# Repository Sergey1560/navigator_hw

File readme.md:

# Navigator HW

Bluetooth-адаптер одометра для программы "[TSD Navigator](http://tsdnavigator.com/index.html)". Аналог [оригинального адаптера](http://tsdnavigator.com/v1/greybox.htm) 

[Схема](./navigator.pdf)

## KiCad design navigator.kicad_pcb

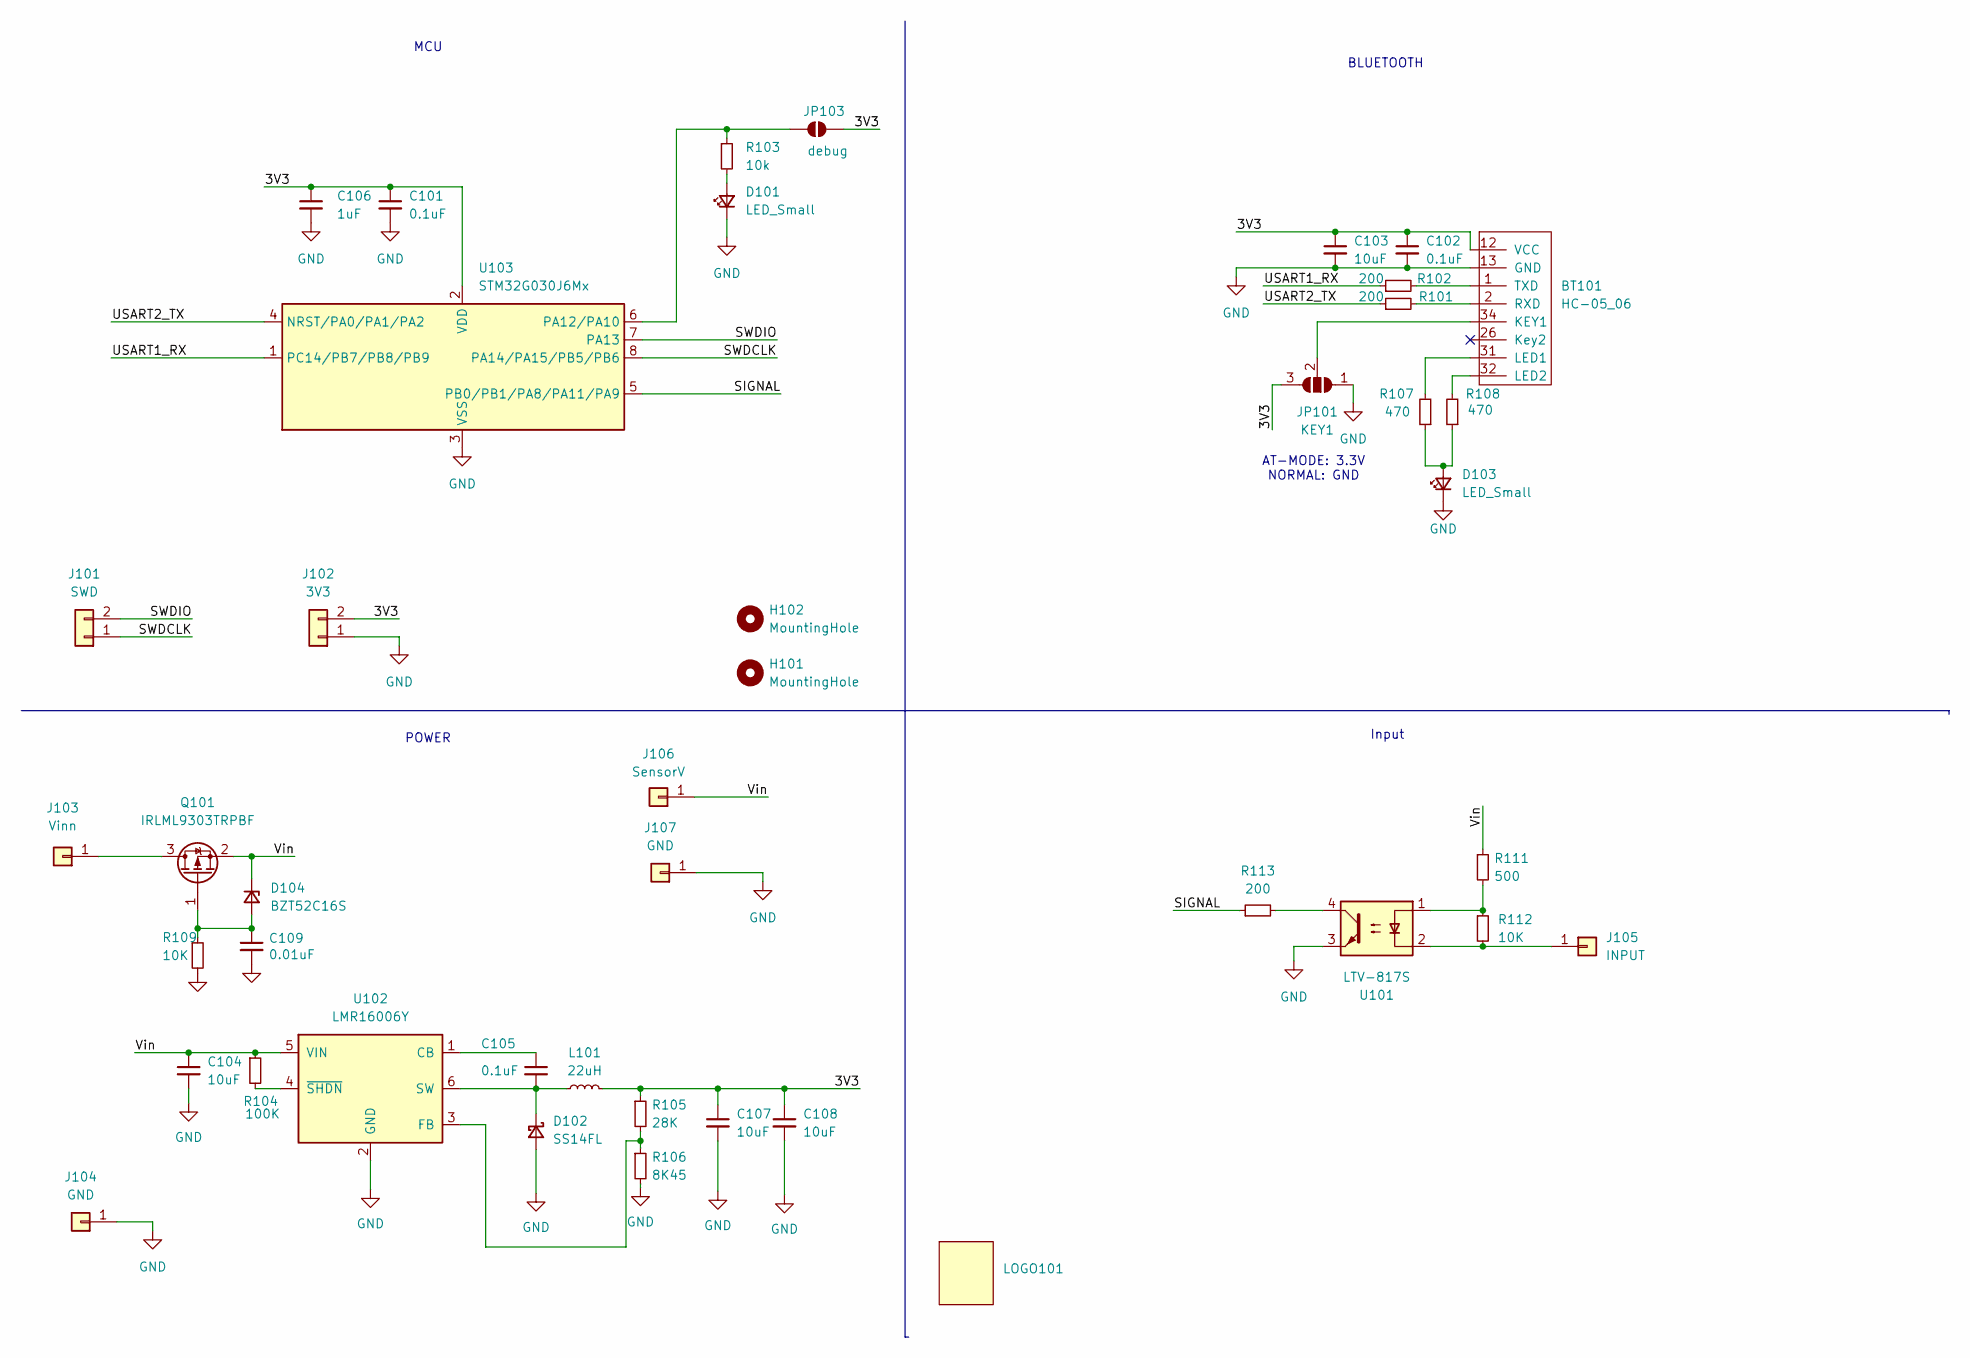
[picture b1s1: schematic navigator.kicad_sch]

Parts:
BT101: HC-05_06; HC-05
C101, C102: 0.1uF; C_0805_2012Metric
C103: 10uF; C_0805_2012Metric
C104, C107, C108: 10uF; C_0805_2012Metric; LCSC C440198
C105: 0.1uF; C_0805_2012Metric; LCSC C14663
C106: 1uF; C_0805_2012Metric
C109: 0.01uF; C_0603_1608Metric
D101, D103: LED_Small; LED_1206_3216Metric
D102: SS14FL; D_SMF; LCSC C111580
D104: BZT52C16S; D_SOD-323
H101, H102: MountingHole; MountingHole_3.2mm_M3
J101: SWD; PinHeader_1x02_P2.54mm_Vertical
J102: 3V3; PinHeader_1x02_P2.54mm_Vertical
J103: Vinn; PinHeader_1x01_P2.54mm_Vertical
J104, J107: GND; PinHeader_1x01_P2.54mm_Vertical
J105: INPUT; PinHeader_1x01_P2.54mm_Vertical
J106: SensorV; PinHeader_1x01_P2.54mm_Vertical
JP101: KEY1; SolderJumper-3_P1.3mm_Open_RoundedPad1.0x1.5mm
JP103: debug; SolderJumper-2_P1.3mm_Open_Pad1.0x1.5mm
L101: 22uH; FNR5040S220MT; LCSC C167971
LOGO101: logo_15x9
Q101: IRLML9303TRPBF; SOT-23
R101, R102, R113: 200; R_0805_2012Metric
R103: 10k; R_0805_2012Metric
R104: 100K; R_0603_1608Metric; LCSC C163504
R105: 28K; R_0603_1608Metric; LCSC C728593
R106: 8K45; R_0603_1608Metric; LCSC C98220
R107, R108: 470; R_0805_2012Metric
R109: 10K; R_0603_1608Metric
R111: 500; R_0805_2012Metric
R112: 10K; R_0805_2012Metric
U101: LTV-817S; SMDIP-4_W9.53mm
U102: LMR16006Y; SOT-23-6; LCSC C290195
U103: STM32G030J6Mx; SOIC-8_3.9x4.9mm_P1.27mm

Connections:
/3V3: BT101.12 (VCC), C101.1, C102.1, C103.1, C106.1, C107.1, C108.1, J102.2, JP101.3 (B), JP103.2 (B), L101.2, R105.1, U103.2 (VDD)
/SIGNAL: R113.1, U103.5 (PB0/PB1/PA8/PA11/PA9)
/SWDCLK: J101.1, U103.8 (PA14/PA15/PB5/PB6)
/SWDIO: J101.2, U103.7 (PA13)
/USART1_RX: R102.1, U103.1 (PC14/PB7/PB8/PB9)
/USART2_TX: R101.1, U103.4 (NRST/PA0/PA1/PA2)
/Vin: C104.1, D104.1 (K), J106.1, Q101.2 (S), R104.1, R111.1, U102.5 (VIN)
GND: BT101.13 (GND), C101.2, C102.2, C103.2, C104.2, C106.2, C107.2, C108.2, C109.2, D101.1 (K), D102.2 (A), D103.1 (K), J102.1, J104.1, J107.1, JP101.1 (A), R106.2, R109.2, U101.3, U102.2 (GND), U103.3 (VSS)
unnamed: BT101.34 (KEY1), JP101.2 (C)
unnamed: BT101.31 (LED1), R107.2
unnamed: BT101.32 (LED2), R108.2
unnamed: BT101.2 (RXD), R101.2
unnamed: BT101.1 (TXD), R102.2
unnamed: D101.2 (A), R103.2
unnamed: C105.2, D102.1 (K), L101.1, U102.6 (SW)
unnamed: D103.2 (A), R107.1, R108.1
unnamed: C109.1, D104.2 (A), Q101.1 (G), R109.1
unnamed: J103.1, Q101.3 (D)
unnamed: J105.1, R112.2, U101.2
unnamed: JP103.1 (A), R103.1, U103.6 (PA12/PA10)
unnamed: R111.2, R112.1, U101.1
unnamed: R113.2, U101.4
unnamed: C105.1, U102.1 (CB)
unnamed: R105.2, R106.1, U102.3 (FB)
unnamed: R104.2, U102.4 (~SHDN)

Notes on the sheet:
MCU
BLUETOOTH
Input
POWER
AT-MODE: 3.3V NORMAL: GND

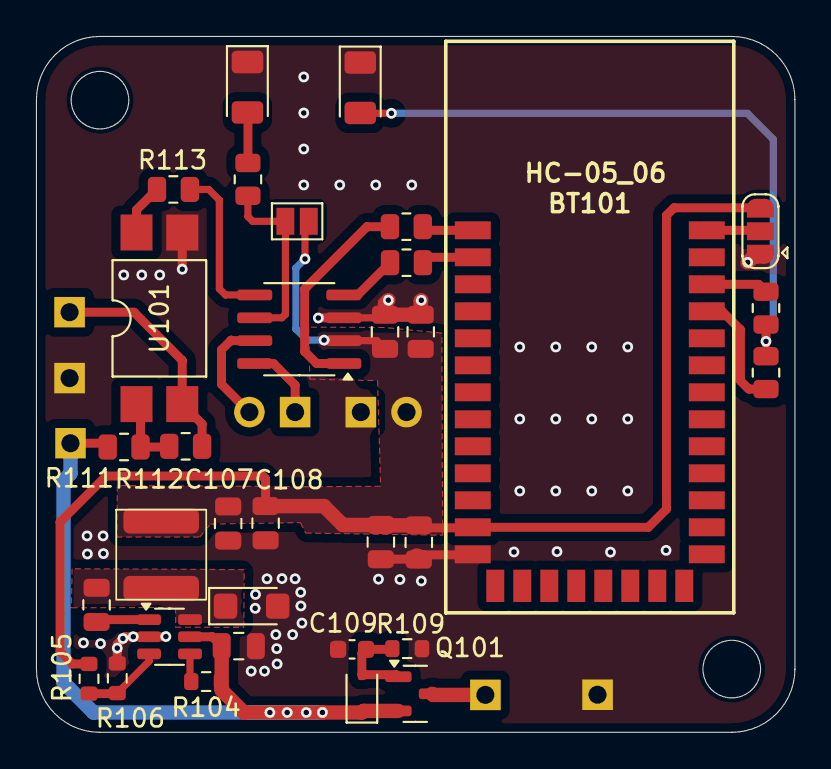
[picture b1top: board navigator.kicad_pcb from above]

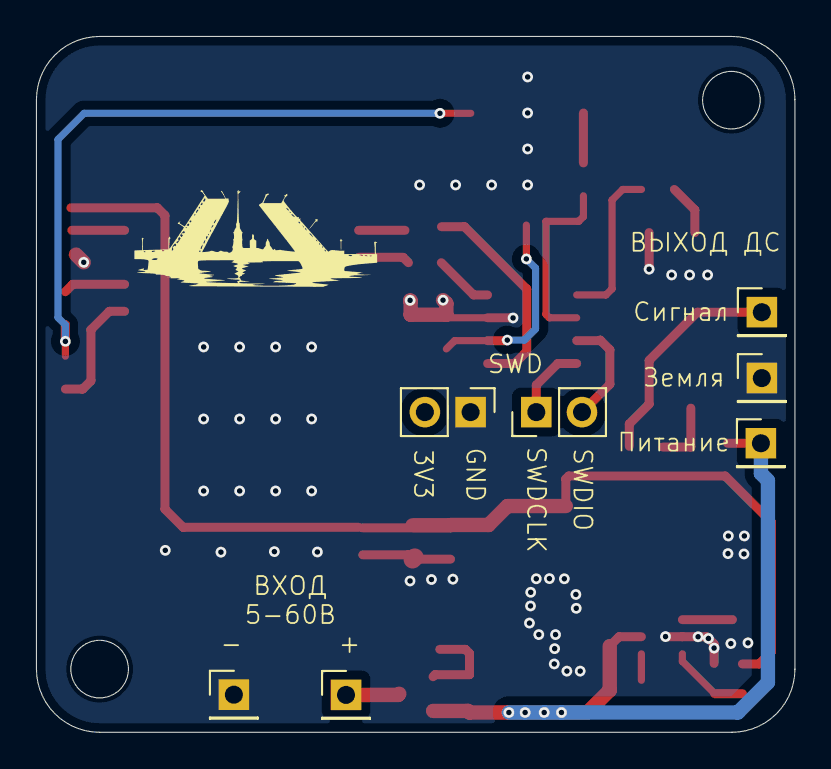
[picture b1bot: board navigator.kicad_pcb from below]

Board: 2 copper layers, 42.1 x 38.7 mm, 43 parts (8 on the bottom side), 25 nets.

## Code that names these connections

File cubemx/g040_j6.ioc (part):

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Mcu.Name=STM32G030J6Mx
Mcu.Package=SO8N
Mcu.UserName=STM32G030J6Mx
PA12\ [PA10].Signal=GPIO_Output
PA13.Mode=Serial_Wire
PA13.Signal=SYS_SWDIO
PA14-BOOT0.Mode=Serial_Wire
PA14-BOOT0.Signal=SYS_SWCLK
PA14-BOOT0__PA15__PB5__PB6.StandardMode=true
PA2.Signal=USART2_TX
PB0__PB1__PA8__PA11\ [PA9].StandardMode=true
PB1.Signal=S_TIM14_CH1
PB7.Signal=USART1_RX
PC14-OSC32_IN\ (PC14)__PB7__PB8__PB9.StandardMode=true
RCC.HSE_VALUE=8000000
RCC.SYSCLKFreq_VALUE=64000000
RCC.SYSCLKSource=RCC_SYSCLKSOURCE_PLLCLK
board=custom

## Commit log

2024-06-26 Initial
2024-06-26 readme
2024-06-29 3d model, prod files
2024-10-24 Production ready
2024-10-24 фото+схема
2024-10-24 readme links
